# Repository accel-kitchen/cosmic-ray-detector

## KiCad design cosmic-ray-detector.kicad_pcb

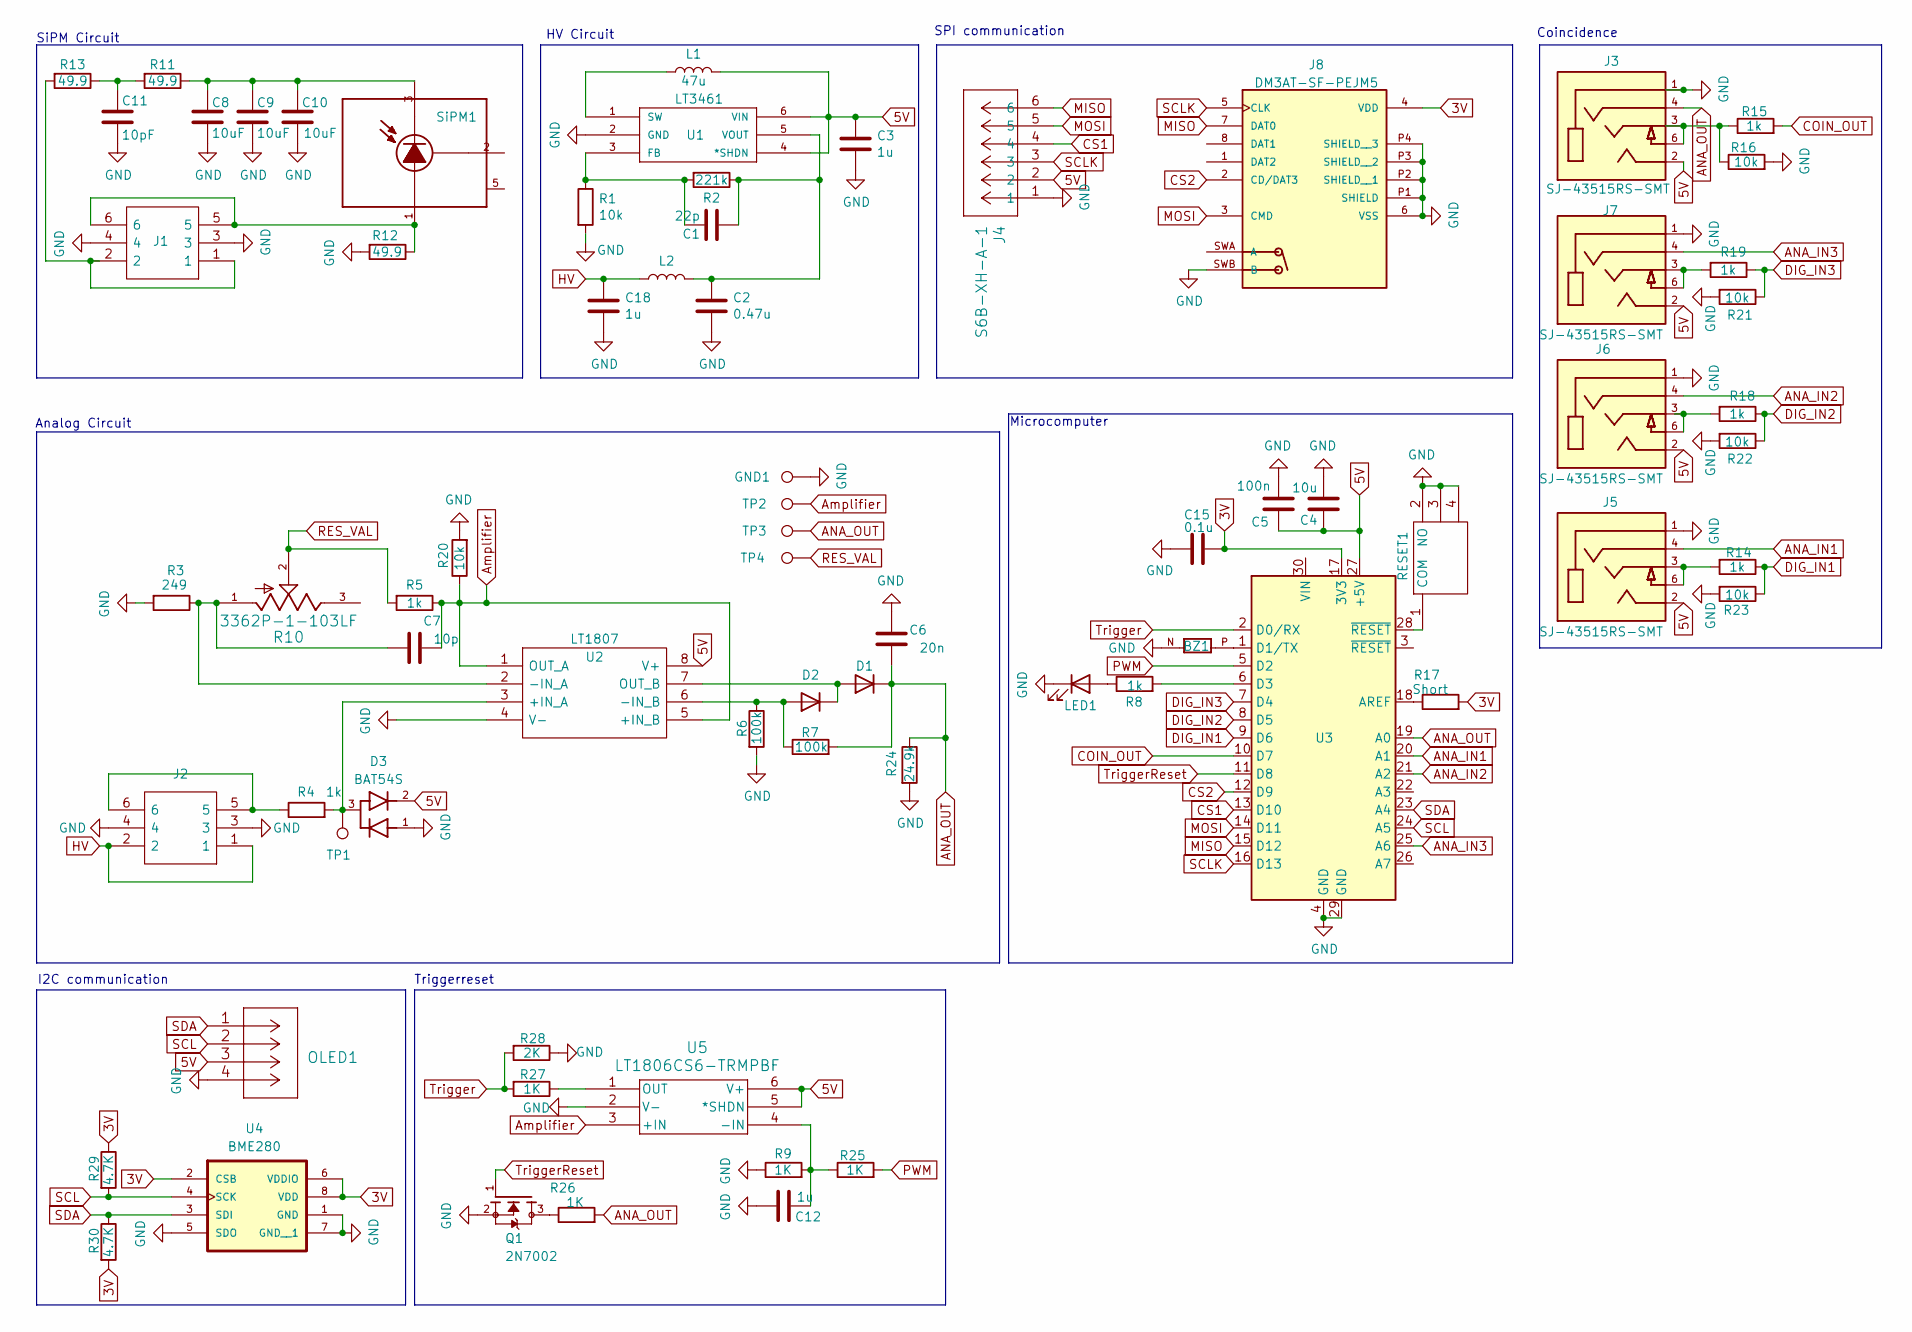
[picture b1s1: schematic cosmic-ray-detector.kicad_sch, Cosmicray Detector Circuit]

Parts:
BZ1: CPT-1117-83-SMT-TR; XDCR_CPT-1117-83-SMT-TR; PARTREV N/A
C1: 22p; C_0805_2012Metric
C2: 0.47u; C_0805_2012Metric
C3, C12, C18: 1u; C_0805_2012Metric
C4: 10u; C_0805_2012Metric
C5: 100n; C_0805_2012Metric
C6: 20n; C_0805_2012Metric
C7: 10p; C_0805_2012Metric
C8, C9, C10: 10uF; C_0805_2012Metric
C11: 10pF; C_0805_2012Metric
C15: 0.1u; C_0805_2012Metric
D1, D2: D; D_SOD-123
D3: BAT54S; SOT95P240X120-3N; PARTREV 2.3
GND1: TestPoint; TestPoint_THTPad_3.0x3.0mm_Drill1.5mm
J1: 15-91-0060; 15910060; Mouser Part Number 538-15-91-0060
J2: 15-91-0060; TE_534998-3; Mouser Part Number 538-15-91-0060
J3, J5, J6, J7: SJ-43515RS-SMT; SJ-43515RS-SMT-TR
J4: S6B-XH-A-1; CONN_S6B-XH-A-1_JST
J8: DM3AT-SF-PEJM5; HRS_DM3AT-SF-PEJM5; PARTREV 20200913
L1: 47u; L_1210_3225Metric
L2: 2500; L_0805_2012Metric
LED1: LED; LED_D3.0mm
OLED1: PPTC041LGBN-RC
Q1: 2N7002; SOT95P240X111-3N; PARTREV 4
R1, R16, R20, R21, R22, R23: 10k; R_0805_2012Metric
R2: 221k; R_0805_2012Metric
R3: 249; R_0805_2012Metric
R4, R5, R8, R14, R15, R18, R19: 1k; R_0805_2012Metric
R6, R7: 100k; R_0805_2012Metric
R9, R25, R26, R27: 1K; R_0805_2012Metric
R10: 3362P-1-103LF; TRIM_3362P-1-103LF; PARTREV 08/26/10
R11, R12, R13: 49.9; R_0805_2012Metric
R17: Short; R_0805_2012Metric
R24: 24.9k; R_0805_2012Metric
R28: 2K; R_0805_2012Metric
R29, R30: 4.7K; R_0805_2012Metric
RESET1: TL1105SF250Q; Mouser Part Number 612-TL1105S-250
SiPM1: MICROFC-60035-SMT-TR1; XDCR_MICROFC-60035-SMT-TR1
TP1, TP2, TP3, TP4: TestPoint; TestPoint_THTPad_3.0x3.0mm_Drill1.5mm
U1: LT3461; TSOT-23-6; MANUFACTURER_PART_NUMBER lt3461es6#trpbf
U2: LT1807; SOIC127P599X175-8N; Mouser Part Number 584-LT1807IS8#PBF
U3: Arduino_Nano_v3.x; Arduino_Nano
U4: BME280; PSON65P250X250X100-8N
U5: LT1806CS6-TRMPBF; TSOT-23-6

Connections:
3V: C15.1, J8.4 (VDD), R17.2, R29.1, R30.2, U3.17 (3V3), U4.2 (CSB), U4.6 (VDDIO), U4.8 (VDD)
5V: C3.1, C4.1, C5.1, D3.2, J3.2, J4.2, J5.2, J6.2, J7.2, L1.2, OLED1.3, U1.4 (*SHDN), U1.6 (VIN), U2.8 (V+), U3.27 (+5V), U5.5 (*SHDN), U5.6 (V+)
ANA_IN1: J5.4, U3.20 (A1)
ANA_IN2: J6.4, U3.21 (A2)
ANA_IN3: J7.4, U3.25 (A6)
ANA_OUT: C6.1, D1.1 (K), J3.4, R7.2, R24.1, R26.2, TP3.1, U3.19 (A0)
Amplifier: C7.2, R5.1, R20.1, TP2.1, U2.1 (OUT_A), U2.5 (+IN_B), U5.3 (+IN)
COIN_OUT: R15.2, U3.10 (D7)
CS1: J4.4, U3.13 (D10)
CS2: J8.2 (CD/DAT3), U3.12 (D9)
DIG_IN1: R14.1, R23.1, U3.9 (D6)
DIG_IN2: R18.1, R22.1, U3.8 (D5)
DIG_IN3: R19.1, R21.1, U3.7 (D4)
GND: BZ1.N, C2.2, C3.2, C4.2, C5.2, C6.2, C8.2, C9.2, C10.2, C11.2, C12.2, C15.2, C18.2, D3.1, GND1.1, J1.3, J1.4, J2.3, J2.4, J3.1, J4.1, J5.1, J6.1, J7.1, J8.6 (VSS), J8.P1 (SHIELD), J8.P2 (SHIELD__1), J8.P3 (SHIELD__2), J8.P4 (SHIELD__3), J8.SWB (B), LED1.1 (K), OLED1.4, Q1.2, R1.2, R3.2, R6.2, R9.1, R12.2, R16.2, R20.2, R21.2, R22.2, R23.2, R24.2, R28.1, RESET1.2 (NO), RESET1.3, RESET1.4, U1.2 (GND), U2.4 (V-), U3.4 (GND), U3.29 (GND), U4.1 (GND), U4.5 (SDO), U4.7 (GND__1), U5.2 (V-)
HV: C18.1, J2.1, J2.2, L2.1
MISO: J4.6, J8.7 (DAT0), U3.15 (D12)
MOSI: J4.5, J8.3 (CMD), U3.14 (D11)
unnamed: C11.1, R11.2, R13.1
unnamed: D1.2 (A), D2.1 (K), U2.7 (OUT_B)
unnamed: D2.2 (A), R6.1, R7.1, U2.6 (-IN_B)
unnamed: J1.1, J1.2, R13.2
unnamed: J2.5, J2.6, R4.1
unnamed: J3.3, J3.6, R15.1, R16.1
unnamed: J5.3, J5.6, R14.2
unnamed: J6.3, J6.6, R18.2
unnamed: J7.3, J7.6, R19.2
unnamed: LED1.2 (A), R8.1
unnamed: Q1.3, R26.1
unnamed: RESET1.1 (COM), U3.28 (~RESET)
unnamed: C8.1, C9.1, C10.1, R11.1, SiPM1.3 (N-CATHODE)
unnamed: J1.5, J1.6, R12.1, SiPM1.1 (P-ANODE)
unnamed: C1.1, R1.1, R2.2, U1.3 (FB)
unnamed: L1.1, U1.1 (SW)
unnamed: C1.2, C2.1, L2.2, R2.1, U1.5 (VOUT)
unnamed: D3.3, R4.2, TP1.1, U2.3 (+IN_A)
unnamed: R17.1, U3.18 (AREF)
unnamed: BZ1.P, U3.1 (D1/TX)
unnamed: R8.2, U3.6 (D3)
unnamed: C12.1, R9.2, R25.1, U5.4 (-IN)
unnamed: R27.1, U5.1 (OUT)
PWM: R25.2, U3.5 (D2)
RES_VAL: R5.2, R10.2, TP4.1
RES_VAL2: C7.1, R3.1, R10.1, U2.2 (-IN_A); also elsewhere on the board
SCL: OLED1.2, R29.2, U3.24 (A5), U4.4 (SCK)
SCLK: J4.3, J8.5 (CLK), U3.16 (D13)
SDA: OLED1.1, R30.1, U3.23 (A4), U4.3 (SDI)
Trigger: R27.2, R28.2, U3.2 (D0/RX)
TriggerReset: Q1.1, U3.11 (D8)

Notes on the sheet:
HV Circuit
I2C communication
SPI communication
Triggerreset
SiPM Circuit
Analog Circuit
Microcomputer
Coincidence

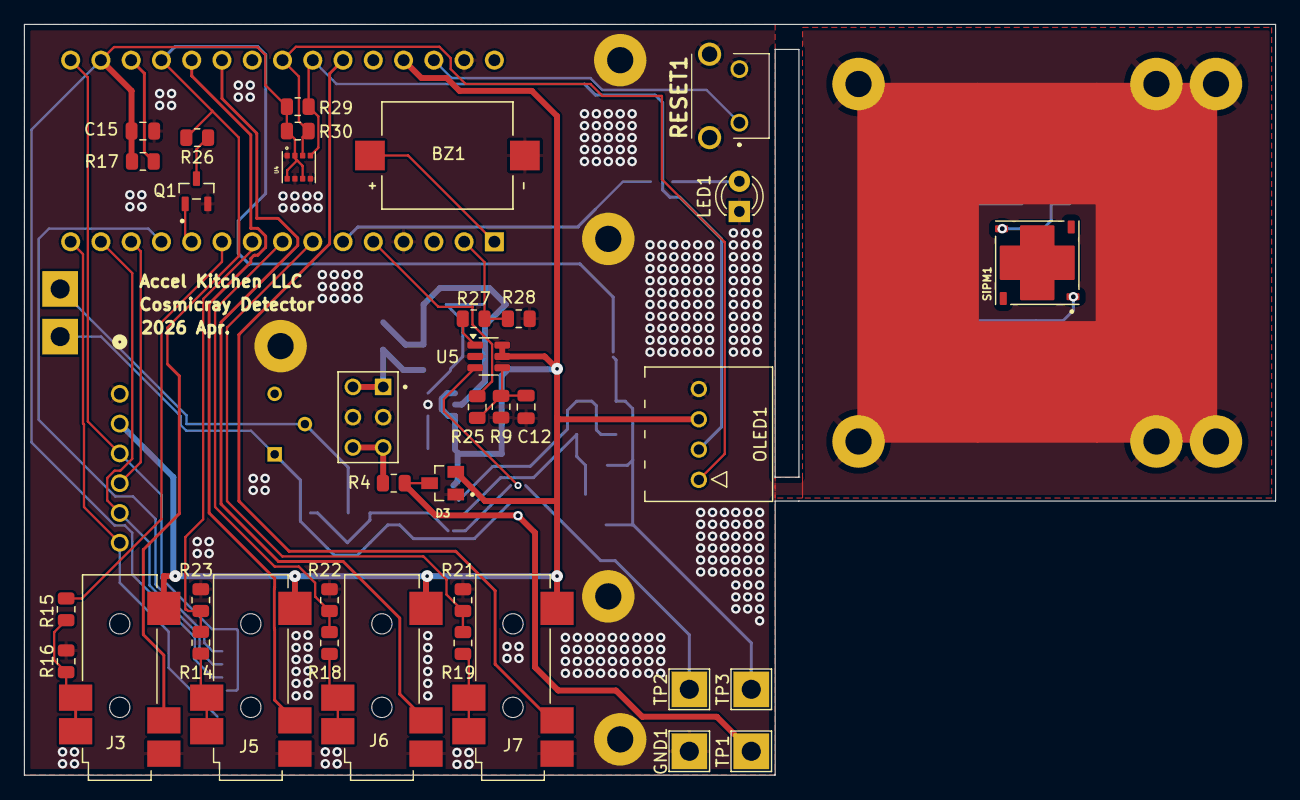
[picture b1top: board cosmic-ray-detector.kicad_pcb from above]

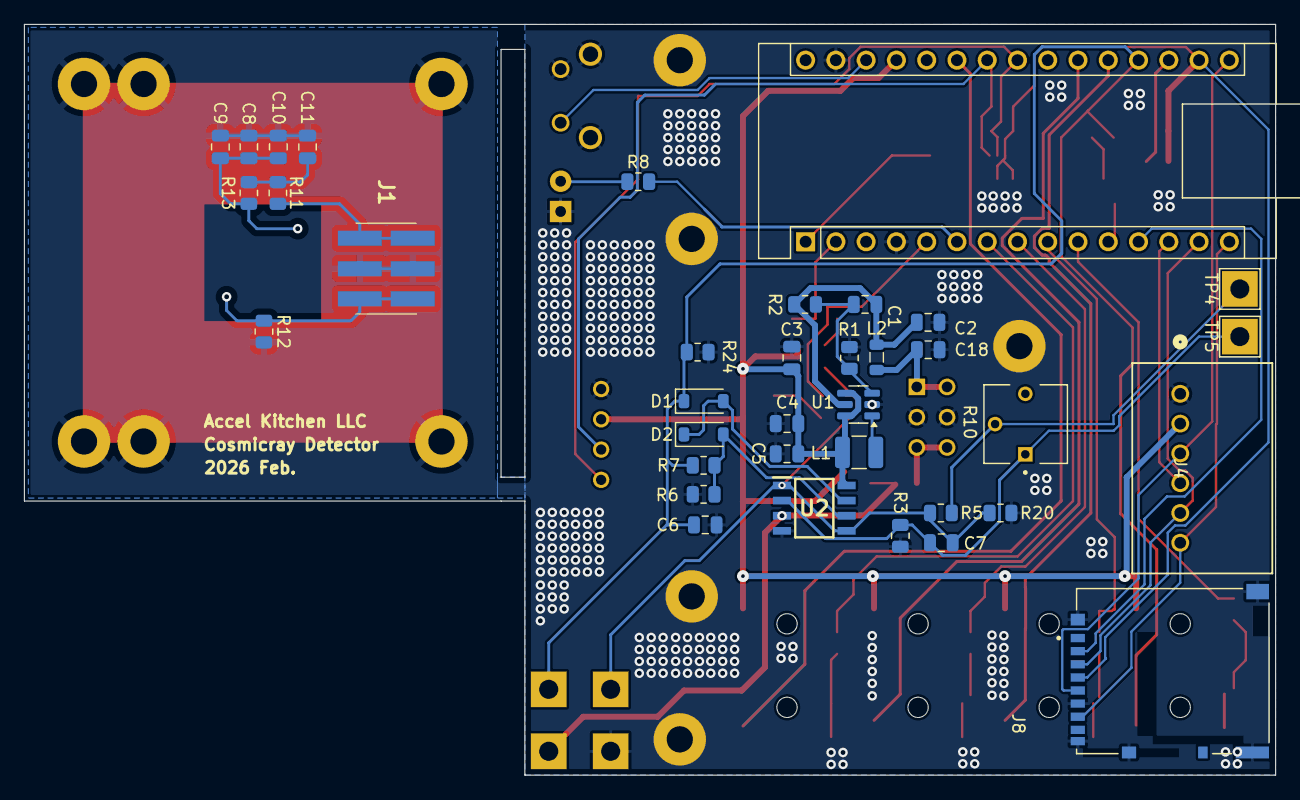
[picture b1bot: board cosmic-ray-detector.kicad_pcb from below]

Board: 2 copper layers, 105.0 x 63.0 mm, 74 parts (37 on the bottom side), 48 nets.

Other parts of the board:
TP5: TestPoint; TestPoint_THTPad_3.0x3.0mm_Drill1.5mm

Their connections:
RES_VAL2: TP5.1; also elsewhere on the board

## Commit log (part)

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2022-09-20 test

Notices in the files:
parts and their libraries:
Copyright 2021 Accelerated Designs. All rights reserved.
